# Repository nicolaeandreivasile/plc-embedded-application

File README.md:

# plc-embedded-application
A PLC (Programmable Logic Controller) made from scratch focused on controlling and maintaining industrial-like applications

## Board design
Control unit schematic under development. I/O unit schematic development process not started yet

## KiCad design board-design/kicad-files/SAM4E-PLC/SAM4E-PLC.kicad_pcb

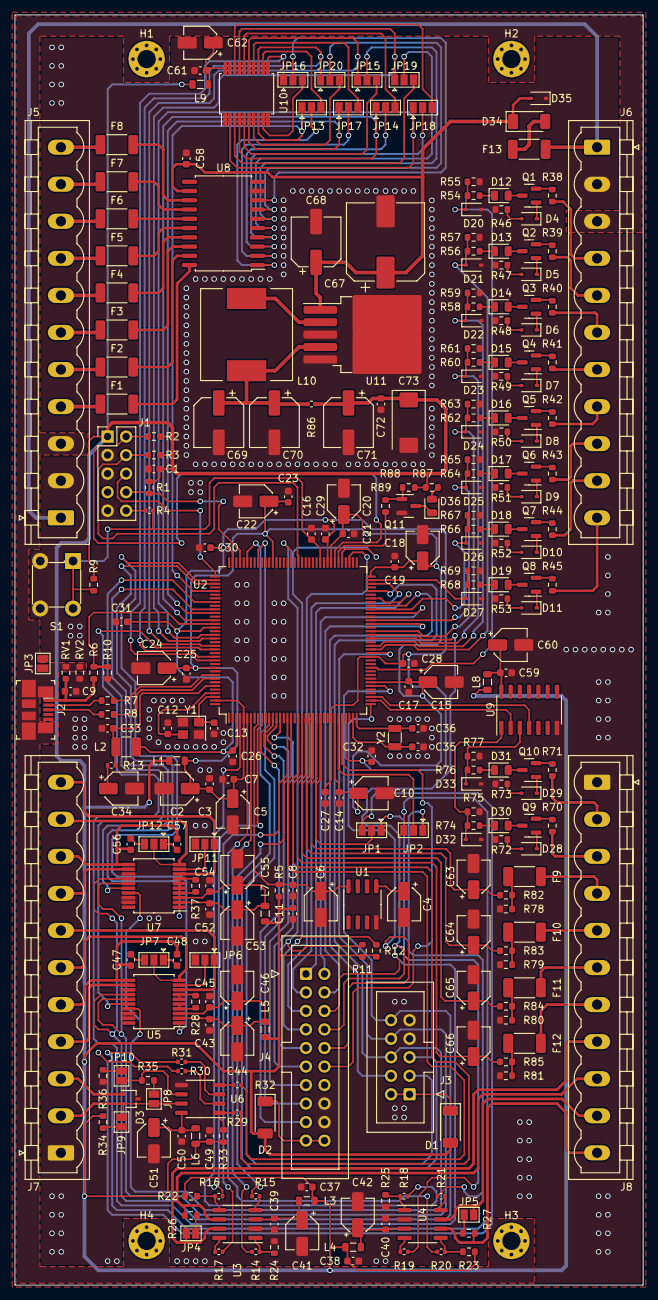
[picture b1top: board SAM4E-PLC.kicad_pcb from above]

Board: 2 copper layers, 86.1 x 174.1 mm, 280 parts (0 on the bottom side), 247 nets.

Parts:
C1, C37, C38, C49, C72: 22uF/6.3V/20%/C0603; C_0603_1608Metric
C2, C5, C10, C15, C18, C20, C22, C24, C34, C41, C42, C44, C46, C51, C53, C55, C60, C62: 10uF/16V/20%/4x5.4mm; CP_Elec_4x5.4
C3, C7, C14, C17, C19, C21, C23, C25, C26, C27, C28, C29, C30, C31, C32, C33, C39, C40, C43, C45, C47, C48, C50, C52, C54, C56, C57, C59, C61: 0.1uF/6.3V/20%/C0603; C_0603_1608Metric
C4, C6, C63, C64, C65, C66: 1uF/16V/20%/4x5.4mm; CP_Elec_4x5.4
C8, C11, C16: 100nF/6.3V/20%/C0603; C_0603_1608Metric
C9: 10pF/6.3V/20%/C0603; C_0603_1608Metric
C12, C13, C35, C36: 12pF/6.3V/10%/C0603; C_0603_1608Metric
C58: 47uF/6.3V/20%/C0603; C_0603_1608Metric
C67: 100uF/63V/20%/10x12.5mm (APD1012101M063R); CP_Elec_10x12.5
C68: 22uF/63V/20%/6.3x6mm (APD0606220M063R); CP_Elec_6.3x5.9
C69: 220uF/16V/20%/6.3x7.7mm; CP_Elec_6.3x7.7
C70, C71: 100uF/16V/20%/6.3x7.7mm; CP_Elec_6.3x7.7
C73: 470uF/16V/20%/C2917/Tantalum; CP_EIA-7343-30_AVX-N
D1, D2: RB068LAM-30TFTR; D_SOD-128
D3: VESD16A2-03G-G3; SOT-323_SC-70
D4, D5, D6, D7, D8, D9, D10, D11, D28, D29: CMDZ12V; D_SOD-323
D12, D13, D14, D15, D16, D17, D18, D19, D30, D31, D36: LED; LED_0805_2012Metric
D20, D21, D22, D23, D24, D25, D26, D27, D32, D33: CMDZ3V6; D_SOD-323
D34: RB088LAM-40TFTR; D_SOD-128
D35: SD36C-01FTG; D_SOD-323
F1, F2, F3, F4, F5, F6, F7, F8, F9, F10, F11, F12, F13: MF-SMDF050; Fuse_2010_5025Metric
H1, H2, H3, H4: MountingHole; MountingHole_2.5mm_Pad_Via
J1: Conn_ARM_JTAG_SWD_10; PinHeader_2x05_P2.54mm_Vertical
J2: 0473460001; USB_Micro_B_Female_0473460001
J3: Conn_02x05_Odd_Even; IDC-Header_2x05_P2.54mm_Vertical
J4: Conn_02x10_Odd_Even; IDC-Header_2x10_P2.54mm_Vertical
J5, J6, J7, J8: Screw_Terminal_01x11; PhoenixContact_MSTBVA_2,5_11-G-5,08_1x11_P5.08mm_Vertical
JP1, JP2, JP6, JP7, JP11, JP12, JP13, JP14, JP15, JP16, JP17, JP18, JP19, JP20: SolderJumper_3_Open; SolderJumper-3_P1.3mm_Open_Pad1.0x1.5mm
JP3, JP4, JP5, JP8, JP9, JP10: SolderJumper_2_Open; SolderJumper-2_P1.3mm_Open_Pad1.0x1.5mm
L1, L3, L4, L5, L6, L7, L8, L9: FB0805/600R/2A; L_0805_2012Metric
L2: 10uH; L_1210_3225Metric
L10: 150uH/12x12mm (SRR1210-151M); L_12x12mm_H8mm
Q1, Q2, Q3, Q4, Q5, Q6, Q7, Q8, Q9, Q10: BC807; SOT-23
Q11: BC817; SOT-23
R1, R2, R3: 100K/R0603; R_0603_1608Metric
R4, R14, R15, R16, R17, R18, R19, R20, R21, R29, R30, R31, R32, R86: 0R(board_mounted); R_0402_1005Metric
R5, R87: 330R/R0603; R_0603_1608Metric
R6: 47K/R0603; R_0603_1608Metric
R7, R8: 27R/R0603; R_0603_1608Metric
R9, R11, R12, R22, R23, R24, R25, R33, R46, R47, R48, R49, R50, R51, R52, R53, R55, R57, R59, R61, R63, R65, R67, R69, R72, R73, R75, R77, R82, R83, R84, R85, R88: 10K/R0603; R_0603_1608Metric
R10: 68K/R0603; R_0603_1608Metric
R13: 1R/R0402; R_0402_1005Metric
R26, R27, R35: 120R/R0603; R_0603_1608Metric
R28, R37: 400R/R0603; R_0603_1608Metric
R34, R36: 420R/R0603; R_0603_1608Metric
R38, R39, R40, R41, R42, R43, R44, R45, R70, R71: 100R/R0603; R_0603_1608Metric
R54, R56, R58, R60, R62, R64, R66, R68, R74, R76: 4.3K/R0603; R_0603_1608Metric
R78, R79, R80, R81: 100R/1W/R0603; R_0603_1608Metric
R89: 1K/R0603; R_0603_1608Metric
RV1, RV2: V5.5MLA0603N; R_0603_1608Metric
S1: 1825910-6; Switch_Tactile_THT_6x6mm
U1: LM385M-ADJ; SOIC-8_3.9x4.9mm_P1.27mm
U2: ATSAM4E16E; LQFP-144_20x20mm_P0.5mm
U3, U4: SN65HVD234; SOIC-8_3.9x4.9mm_P1.27mm
U5, U7: MAX31865xAP; SSOP-20_5.3x7.2mm_P0.65mm
U6: MAX3485ESA+T; SO-8_3.9x4.9mm_P1.27mm
U8: ULN2803CDWR; SOIC-20W_7.5x12.8mm_P1.27mm
U9: 74AC14SCX; SOIC-14_3.9x8.7mm_P1.27mm
U10: SN74HC240DBR; SSOP-20_5.3x7.2mm_P0.65mm
U11: LM2576HVS-3.3; TO-263-5_TabPin3
Y1: ECS-160-8-33B-CTN-TR; Crystal_SMD_3225-4Pin_3.2x2.5mm
Y2: FC-135 32.7680KA-AG0; Crystal_SMD_3215-2Pin_3.2x1.5mm

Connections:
+3V3: C1.1, C11.1, C37.1, C38.1, C49.1, C71.1, C72.1, C73.1, D1.2 (A), D2.2 (A), J1.1 (VTref), L1.1, L3.1, L4.1, L5.1, L6.1, L7.1, L8.1, L9.1, R1.2, R2.2, R3.2, R5.1, R9.1, R11.1, R12.1, R22.1, R23.1, R33.1, R34.1, R86.2, R87.1, R88.1
+24V: C58.1, C67.1, C68.1, D34.1 (K), D35.2 (A2), U8.12 (COM), U11.1 (VIN)
/CAN0_D: JP1.1 (A), R19.1
/CAN0_EN: R20.1, U2.6 (PE1)
/CAN0_R: JP2.1 (A), R21.1
/CAN0_RS: R18.1, U2.4 (PE0)
/CAN1_D: R15.1, U2.18 (PC15)
/CAN1_EN: R16.1, U2.10 (PE3)
/CAN1_R: R17.1, U2.17 (PC12)
/CAN1_RS: R14.1, U2.7 (PE2)
/CNT0: U2.38 (PC1), U9.2 (~O0)
/CNT1: U2.39 (PC2), U9.4 (~O1)
/ESP32_INT: J3.5, U2.103 (PC17)
/I2C_SCL: J4.7, R12.2, U2.77 (PA4/PGMNCMD)
/I2C_SDA: J4.9, R11.2, U2.91 (PA3)
/IO/AI0: C66.1, R85.2, U2.22 (PA20/PGMD8)
/IO/AI1: C65.1, R84.2, U2.23 (PA19/PGMD7)
/IO/AI2: C64.1, R83.2, U2.24 (PA18/PGMD6)
/IO/AI3: C63.1, R82.2, U2.25 (PA17/PGMD5)
/IO/DI0: D20.1 (K), R54.2, R55.1, U2.47 (PD27)
/IO/DI1: D21.1 (K), R56.2, R57.1, U2.52 (PD25)
/IO/DI2: D22.1 (K), R58.2, R59.1, U2.53 (PD26)
/IO/DI3: D23.1 (K), R60.2, R61.1, U2.55 (PD24)
/IO/DI4: D24.1 (K), R62.2, R63.1, U2.57 (PD23)
/IO/DI5: D25.1 (K), R64.2, R65.1, U2.60 (PD22)
/IO/DI6: D26.1 (K), R66.2, R67.1, U2.63 (PD21)
/IO/DI7: D27.1 (K), R68.2, R69.1, U2.71 (PD28)
/IO/DO0: JP18.1 (A), U2.125 (PD5), U10.2 (1A1)
/IO/DO1: JP14.1 (A), U2.121 (PD6), U10.4 (1A2)
/IO/DO2: JP17.1 (A), U2.119 (PD7), U10.6 (1A3)
/IO/DO3: JP13.1 (A), U2.113 (PD8), U10.8 (1A4)
/IO/DO4: JP16.1 (A), U2.132 (PD1), U10.11 (2A1)
/IO/DO5: JP20.1 (A), U2.131 (PD2), U10.13 (2A2)
/IO/DO6: JP15.1 (A), U2.128 (PD3), U10.15 (2A3)
/IO/DO7: JP19.1 (A), U2.126 (PD4), U10.17 (2A4)
/IO/MCV_AI0: F12.1, J8.7
/IO/MCV_AI1: F11.1, J8.6
/IO/MCV_AI2: F10.1, J8.5
/IO/MCV_AI3: F9.1, J8.4
/IO/MCV_CNT0: J8.2, R71.1
/IO/MCV_CNT1: J8.3, R70.1
/IO/MCV_DI0: J6.4, R38.1
/IO/MCV_DI1: J6.5, R39.1
/IO/MCV_DI2: J6.6, R40.1
/IO/MCV_DI3: J6.7, R41.1
/IO/MCV_DI4: J6.8, R42.1
/IO/MCV_DI5: J6.9, R43.1
/IO/MCV_DI6: J6.10, R44.1
/IO/MCV_DI7: J6.11, R45.1
/IO/MCV_DO0: F4.2, J5.7
/IO/MCV_DO1: F3.2, J5.6
/IO/MCV_DO2: F2.2, J5.5
/IO/MCV_DO3: F1.2, J5.4
/IO/MCV_DO4: F8.2, J5.11
/IO/MCV_DO5: F7.2, J5.10
/IO/MCV_DO6: F6.2, J5.9
/IO/MCV_DO7: F5.2, J5.8
/IO/~DO0: JP18.3 (B), U10.18 (1Y1)
/IO/~DO1: JP14.3 (B), U10.16 (1Y2)
/IO/~DO2: JP17.3 (B), U10.14 (1Y3)
/IO/~DO3: JP13.3 (B), U10.12 (1Y4)
/IO/~DO4: JP16.3 (B), U10.9 (2Y1)
/IO/~DO5: JP20.3 (B), U10.7 (2Y2)
/IO/~DO6: JP15.3 (B), U10.5 (2Y3)
/IO/~DO7: JP19.3 (B), U10.3 (2Y4)
/LTE_AP_READY: J4.11, U2.15 (PC30)
/LTE_PWRKEY: J4.15, U2.13 (PC26)
/LTE_RESET_N: J4.17, U2.12 (PC27)
/LTE_STATUS: J4.13, U2.14 (PC31)
/LTE_UART_CTS: J4.4, U2.59 (PA25/PGMD13)
/LTE_UART_DBG_RXD: J4.5, U2.75 (PA9/PGMM1)
/LTE_UART_DBG_TXD: J4.1, U2.66 (PA10/PGMM2)
/LTE_UART_DCD: J4.2, U2.62 (PA26/PGMD14)
/LTE_UART_DTR: J4.3, U2.70 (PA27/PGMD15)
/LTE_UART_RI: J4.6, U2.129 (PA29)
/LTE_UART_RTS: J4.8, U2.56 (PA24/PGMD12)
/LTE_UART_RXD: J4.12, U2.32 (PA21/PGMD9)
/LTE_UART_TXD: J4.10, U2.37 (PA22/PGMD10)
/PWR_LED: R89.2, U2.78 (PD16)
/RS_DE: JP2.3 (B), R31.1
/RS_DI: R32.1, U2.20 (PB1)
/RS_RO: R29.1, U2.21 (PB0)
/SAM4E_INT: J3.3, U2.100 (PC16)
/SPI_CS0: J3.4, U2.64 (PA11/PGMM3)
/SPI_CS1: U2.118 (PA31), U7.16 (~CS)
/SPI_CS2: U2.116 (PA30), U5.16 (~CS)
/SPI_MISO: J3.6, U2.68 (PA12/PGMD0), U5.17 (SDO), U7.17 (SDO)
/SPI_MOSI: J3.10, U2.42 (PA13/PGMD1), U5.14 (SDI), U7.14 (SDI)
/SPI_SCK: J3.8, U2.51 (PA14/PGMD2), U5.15 (SCLK), U7.15 (SCLK)
/VBUS: R6.2, R10.1, U2.122 (PC21)
/~NRST: C16.1, R4.2, R9.2, S1.1, S1.2, U2.83 (~NRST)
/~RS_RE: JP1.3 (B), R30.1
/~RTD0_DRDY: U2.110 (PD9), U5.1 (~DRDY)
/~RTD1_DRDY: U2.111 (PC18), U7.1 (~DRDY)
Earth_Protective: J2.SH, J5.3, J6.3, JP3.2 (B), RV1.2, RV2.2
GND: C1.2, C2.2, C3.2, C4.2, C5.2, C6.2, C7.2, C8.2, C9.2, C10.2, C11.2, C12.1, C13.1, C14.2, C15.2, C16.2, C17.2, C18.2, C19.2, C20.2, C21.2, C22.2, C23.2, C24.2, C25.2, C26.2, C27.2, C28.2, C29.2, C30.2, C31.2, C32.2, C33.2, C34.2, C35.1, C36.1, C37.2, C38.2, C39.2, C40.2, C41.2, C42.2, C43.2, C44.2, C45.2, C46.2, C49.2, C50.2, C51.2, C52.2, C53.2, C54.2, C55.2, C58.2, C59.2, C60.2, C61.2, C62.2, C63.2, C64.2, C65.2, C66.2, C67.2, C68.2, C69.2, C70.2, C71.2, C72.2, C73.2, D3.3 (common), D20.2 (A), D21.2 (A), D22.2 (A), D23.2 (A), D24.2 (A), D25.2 (A), D26.2 (A), D27.2 (A), D32.2 (A), D33.2 (A), D35.1 (A1), J1.3 (GND), J1.5 (GND), J1.9 (GNDDetect), J2.5, J3.7, J3.9, J4.16, J4.18, J5.2, J6.2, J7.1, J8.1, JP3.1 (A), JP6.3 (B), JP11.3 (B), Q11.2 (E), R10.2, R24.2, R25.2, R36.1, R46.2, R47.2, R48.2, R49.2, R50.2, R51.2, R52.2, R53.2, R55.2, R57.2, R59.2, R61.2, R63.2, R65.2, R67.2, R69.2, R72.2, R73.2, R75.2, R77.2, R78.1, R79.1, R80.1, R81.1, RV2.1, S1.3, S1.4, U1.4 (A), U2.8 (GND), U2.44 (GND), U2.61 (GND), U2.95 (GND), U2.115 (GND), U2.135 (GND), U2.138 (GND), U3.2 (GND), U4.2 (GND), U5.13 (GND), U5.18 (DGND), U5.19 (GND), U6.5 (GND), U7.13 (GND), U7.18 (DGND), U7.19 (GND), U8.9 (GND), U9.7 (GND), U10.1 (~1OE), U10.10 (GND), U10.19 (~2OE), U11.3 (GND), U11.5 (~ON/OFF), Y1.2, Y1.4
MCV_CAN0_H: J8.10, JP5.2 (B), U4.7 (CANH)
MCV_CAN0_L: J8.11, R27.1, U4.6 (CANL)
MCV_CAN1_H: J8.8, JP4.2 (B), U3.7 (CANH)
MCV_CAN1_L: J8.9, R26.1, U3.6 (CANL)
MCV_RS_A: D3.1 (A1), J7.3, JP10.2 (B), R35.1, U6.6 (A)
MCV_RS_B: D3.2 (A2), J7.2, JP8.2 (B), JP9.1 (A), U6.7 (B)
MCV_RTD0_FORCE+: J7.7, JP6.1 (A), U5.8 (FORCE+)
MCV_RTD0_FORCE-: J7.4, U5.12 (FORCE-)
MCV_RTD0_RTDIN+: J7.6, JP7.2 (C), U5.10 (RTDIN+)
MCV_RTD0_RTDIN-: C47.1, C48.1, J7.5, U5.11 (RTDIN-)
MCV_RTD1_FORCE+: J7.11, JP11.1 (A), U7.8 (FORCE+)
MCV_RTD1_FORCE-: J7.8, U7.12 (FORCE-)
MCV_RTD1_RTDIN+: J7.10, JP12.2 (C), U7.10 (RTDIN+)
MCV_RTD1_RTDIN-: C56.1, C57.1, J7.9, U7.11 (RTDIN-)
unnamed: C9.1, J2.1, R6.1, RV1.1
unnamed: C34.1, R13.2
unnamed: D1.1 (K), J3.1, J3.2
unnamed: D2.1 (K), J4.19, J4.20
unnamed: D4.2 (A), R46.1
unnamed: D4.1 (K), Q1.1 (B)
unnamed: D5.2 (A), R47.1
unnamed: D5.1 (K), Q2.1 (B)
unnamed: D6.2 (A), R48.1
unnamed: D6.1 (K), Q3.1 (B)
unnamed: D7.2 (A), R49.1
unnamed: D7.1 (K), Q4.1 (B)
unnamed: D8.2 (A), R50.1
unnamed: D8.1 (K), Q5.1 (B)
unnamed: D9.2 (A), R51.1
unnamed: D9.1 (K), Q6.1 (B)
unnamed: D10.2 (A), R52.1
unnamed: D10.1 (K), Q7.1 (B)
unnamed: D11.2 (A), R53.1
unnamed: D11.1 (K), Q8.1 (B)
unnamed: D12.2 (A), Q1.3 (C)
unnamed: D12.1 (K), R54.1
unnamed: D13.2 (A), Q2.3 (C)
unnamed: D13.1 (K), R56.1
unnamed: D14.2 (A), Q3.3 (C)
unnamed: D14.1 (K), R58.1
unnamed: D15.2 (A), Q4.3 (C)
unnamed: D15.1 (K), R60.1
unnamed: D16.2 (A), Q5.3 (C)
unnamed: D16.1 (K), R62.1
unnamed: D17.2 (A), Q6.3 (C)
unnamed: D17.1 (K), R64.1
unnamed: D18.2 (A), Q7.3 (C)
unnamed: D18.1 (K), R66.1
unnamed: D19.2 (A), Q8.3 (C)
unnamed: D19.1 (K), R68.1
unnamed: D28.2 (A), R72.1
unnamed: D28.1 (K), Q9.1 (B)
unnamed: D29.2 (A), R73.1
unnamed: D29.1 (K), Q10.1 (B)
unnamed: D30.2 (A), Q9.3 (C)
unnamed: D30.1 (K), R74.1
unnamed: D31.2 (A), Q10.3 (C)
unnamed: D31.1 (K), R76.1
unnamed: D32.1 (K), R74.2, R75.1, U9.1 (I0)
unnamed: D33.1 (K), R76.2, R77.1, U9.3 (I1)
unnamed: D34.2 (A), F13.2
unnamed: D36.2 (A), R87.2
unnamed: D36.1 (K), Q11.3 (C)
unnamed: F9.2, R78.2, R82.1
unnamed: F10.2, R79.2, R83.1
unnamed: F11.2, R80.2, R84.1
unnamed: F12.2, R81.2, R85.1
unnamed: J1.8 (NC/TDI), R1.1, U2.105 (PB4)
unnamed: J1.4 (SWCLK/TCK), R3.1, U2.89 (PB7)
unnamed: J1.2 (SWDIO/TMS), R2.1, U2.79 (PB6)
unnamed: J1.6 (SWO/TDO), U2.109 (PB5)
unnamed: J1.10 (~RESET), R4.1
unnamed: J2.2, R7.1
unnamed: J2.3, R8.1
unnamed: JP1.2 (C), U2.26 (PB2)
unnamed: JP2.2 (C), U2.31 (PB3)
unnamed: JP4.1 (A), R26.2
unnamed: JP5.1 (A), R27.2
unnamed: JP6.2 (C), U5.9 (FORCE2)
unnamed: C48.2, JP7.1 (A)
unnamed: C47.2, JP7.3 (B)
unnamed: JP8.1 (A), R35.2
unnamed: JP9.2 (B), R34.2
unnamed: JP10.1 (A), R36.2
unnamed: JP11.2 (C), U7.9 (FORCE2)
unnamed: C57.2, JP12.1 (A)
unnamed: C56.2, JP12.3 (B)
unnamed: JP13.2 (C), U8.1 (1B)
unnamed: JP14.2 (C), U8.3 (3B)
unnamed: JP15.2 (C), U8.6 (6B)
unnamed: JP16.2 (C), U8.8 (8B)
unnamed: JP17.2 (C), U8.2 (2B)
unnamed: JP18.2 (C), U8.4 (4B)
unnamed: JP19.2 (C), U8.5 (5B)
unnamed: JP20.2 (C), U8.7 (7B)
unnamed: Q1.2 (E), R38.2
unnamed: Q2.2 (E), R39.2
unnamed: Q3.2 (E), R40.2
unnamed: Q4.2 (E), R41.2
unnamed: Q5.2 (E), R42.2
unnamed: Q6.2 (E), R43.2
unnamed: Q7.2 (E), R44.2
unnamed: Q8.2 (E), R45.2
unnamed: Q9.2 (E), R70.2
unnamed: Q10.2 (E), R71.2
unnamed: Q11.1 (B), R88.2, R89.1
unnamed: C4.1, U1.5 (FB)
unnamed: C6.1, C8.1, R5.2, U1.8 (K), U2.9 (ADVREFP)
unnamed: C35.2, U2.35 (PA7/PGMNVALID), Y2.2
unnamed: C36.2, U2.36 (PA8/PGMM0), Y2.1
unnamed: C12.2, U2.141 (PB8), Y1.3
unnamed: C13.2, U2.142 (PB9), Y1.1
unnamed: R7.2, U2.136 (PB10)
unnamed: R8.2, U2.137 (PB11)
unnamed: C2.1, C3.1, C5.1, C7.1, C10.1, C14.1, C15.1, C17.1, C18.1, C19.1, C20.1, C21.1, C22.1, C23.1, C24.1, C25.1, L1.2, U2.5 (VDDIN), U2.30 (VDDIO), U2.43 (VDDIO), U2.72 (VDDIO), U2.80 (VDDIO), U2.96 (VDDIO), U2.134 (VDDIO), U2.143 (VDDIO)
unnamed: C26.1, C27.1, C28.1, C29.1, C30.1, C31.1, C32.1, L2.1, U2.3 (VDDOUT), U2.29 (VDDCORE), U2.33 (VDDCORE), U2.50 (VDDCORE), U2.81 (VDDCORE), U2.107 (VDDCORE), U2.123 (VDDCORE)
unnamed: C33.1, L2.2, R13.1, U2.139 (VDDPLL)
unnamed: R14.2, R24.1, U3.1 (D)
unnamed: R16.2, R22.2, U3.5 (EN)
unnamed: R15.2, U3.4 (R)
unnamed: R17.2, U3.8 (Rs)
unnamed: C39.1, C41.1, L3.2, U3.3 (VCC)
unnamed: R18.2, R25.1, U4.1 (D)
unnamed: R20.2, R23.2, U4.5 (EN)
unnamed: R19.2, U4.4 (R)
unnamed: R21.2, U4.8 (Rs)
unnamed: C40.1, C42.1, L4.2, U4.3 (VCC)
unnamed: R28.1, U5.4 (BIAS), U5.5 (REFIN+)
unnamed: C43.1, C44.1, C45.1, C46.1, L5.2, U5.2 (DVDD), U5.3 (VDD)
unnamed: R28.2, U5.6 (REFIN-), U5.7 (ISENSOR)
unnamed: R31.2, U6.3 (DE)
unnamed: R32.2, U6.4 (DI)
unnamed: R29.2, R33.2, U6.1 (RO)
unnamed: C50.1, C51.1, L6.2, U6.8 (VCC)
unnamed: R30.2, U6.2 (~RE)
unnamed: R37.1, U7.4 (BIAS), U7.5 (REFIN+)
unnamed: C52.1, C53.1, C54.1, C55.1, L7.2, U7.2 (DVDD), U7.3 (VDD)
unnamed: R37.2, U7.6 (REFIN-), U7.7 (ISENSOR)
unnamed: F1.1, U8.20 (1C)
unnamed: F2.1, U8.19 (2C)
unnamed: F3.1, U8.18 (3C)
unnamed: F4.1, U8.17 (4C)
unnamed: F5.1, U8.16 (5C)
unnamed: F6.1, U8.15 (6C)
unnamed: F7.1, U8.14 (7C)
unnamed: F8.1, U8.13 (8C)
unnamed: C59.1, C60.1, L8.2, U9.14 (VCC)
unnamed: C61.1, C62.1, L9.2, U10.20 (VCC)
unnamed: C69.1, C70.1, L10.2, R86.1, U11.4 (FB)
unnamed: L10.1, U11.2 (OUT)
VIN_24V: F13.1, J5.1, J6.1

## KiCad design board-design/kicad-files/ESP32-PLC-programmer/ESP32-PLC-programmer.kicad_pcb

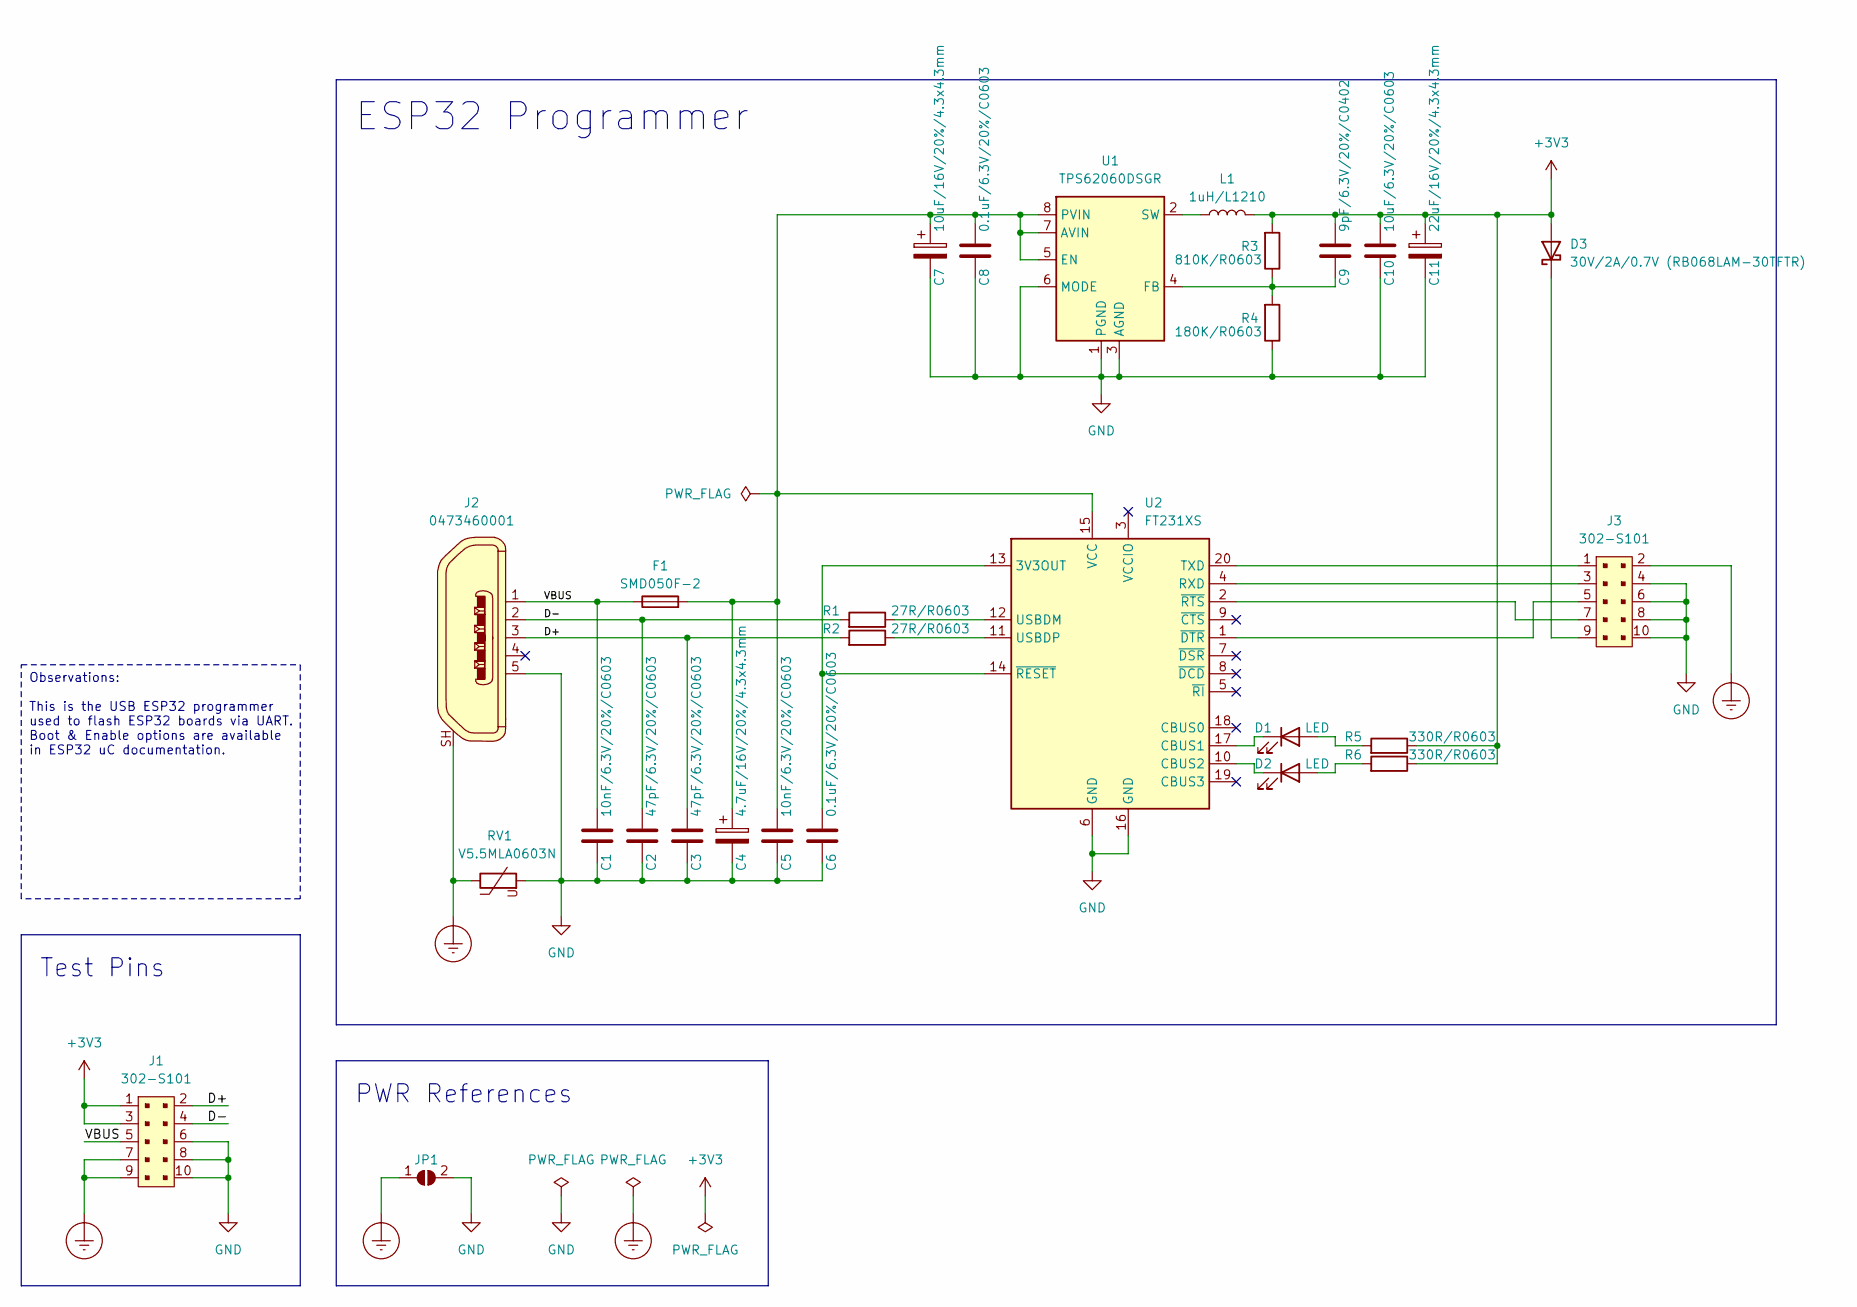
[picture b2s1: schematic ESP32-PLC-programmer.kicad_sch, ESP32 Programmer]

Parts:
C1, C5: 10nF/6.3V/20%/C0603; C_0603_1608Metric
C2, C3: 47pF/6.3V/20%/C0603; C_0603_1608Metric
C4: 4.7uF/16V/20%/4.3x4.3mm; CP_Elec_4x5.4
C6, C8: 0.1uF/6.3V/20%/C0603; C_0603_1608Metric
C7: 10uF/16V/20%/4.3x4.3mm; CP_Elec_4x5.4
C9: 9pF/6.3V/20%/C0402; C_0402_1005Metric
C10: 10uF/6.3V/20%/C0603; C_0603_1608Metric
C11: 22uF/16V/20%/4.3x4.3mm; CP_Elec_4x5.4
D1, D2: LED; LED_0805_2012Metric
D3: 30V/2A/0.7V (RB068LAM-30TFTR); D_SOD-128
F1: SMD050F-2; Fuse_2920_7451Metric
J1, J3: 302-S101; IDC-Header_2x05_P2.54mm_Vertical; MPN 302-S101; Digi-Key_PN ED1543-ND
J2: 0473460001; USB_Micro_B_Female_0473460001; MPN 0473460001; Digi-Key_PN WM17141CT-ND
JP1: SolderJumper_2_Open; SolderJumper-2_P1.3mm_Open_Pad1.0x1.5mm
L1: 1uH/L1210; L_1210_3225Metric
R1, R2: 27R/R0603; R_0603_1608Metric
R3: 810K/R0603; R_0603_1608Metric
R4: 180K/R0603; R_0603_1608Metric
R5, R6: 330R/R0603; R_0603_1608Metric
RV1: V5.5MLA0603N; R_0603_1608Metric
U1: TPS62060DSGR; WSON-8-1EP_2x2mm_P0.5mm_EP0.9x1.6mm_ThermalVias
U2: FT231XS; SSOP-20_3.9x8.7mm_P0.635mm

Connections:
+3V3: C9.1, C10.1, C11.1, D3.2 (A), J1.1, J1.3, L1.2, R3.2, R5.1, R6.1
/D+: C3.1, J1.2, J2.3, R2.2
/D-: C2.1, J1.4, J2.2, R1.2
/VBUS: C1.1, F1.1, J1.5, J2.1
Earth_Protective: J1.7, J1.9, J2.SH, J3.2, JP1.1 (A), RV1.1
GND: C1.2, C2.2, C3.2, C4.2, C5.2, C6.2, C7.2, C8.2, C10.2, C11.2, J1.6, J1.8, J1.10, J2.5, J3.4, J3.6, J3.8, J3.10, JP1.2 (B), R4.1, RV1.2, U1.1 (PGND), U1.3 (AGND), U1.6 (MODE), U2.6 (GND), U2.16 (GND)
unnamed: D1.2 (A), R5.2
unnamed: D1.1 (K), U2.17 (CBUS1)
unnamed: D2.2 (A), R6.2
unnamed: D2.1 (K), U2.10 (CBUS2)
unnamed: D3.1 (K), J3.9
unnamed: C4.1, C5.1, C7.1, C8.1, F1.2, U1.5 (EN), U1.7 (AVIN), U1.8 (PVIN), U2.15 (VCC)
unnamed: C9.2, R3.1, R4.2, U1.4 (FB)
unnamed: L1.1, U1.2 (SW)
unnamed: C6.1, U2.13 (3V3OUT), U2.14 (~RESET)
unnamed: J3.3, U2.4 (RXD)
unnamed: J3.1, U2.20 (TXD)
unnamed: R1.1, U2.12 (USBDM)
unnamed: R2.1, U2.11 (USBDP)
unnamed: J3.5, U2.1 (~DTR)
unnamed: J3.7, U2.2 (~RTS)

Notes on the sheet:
Observations: This is the USB ESP32 programmer used to flash ESP32 boards via UART. Boot & Enable options are available in ESP32 uC documentation.
PWR References
Test Pins
ESP32 Programmer

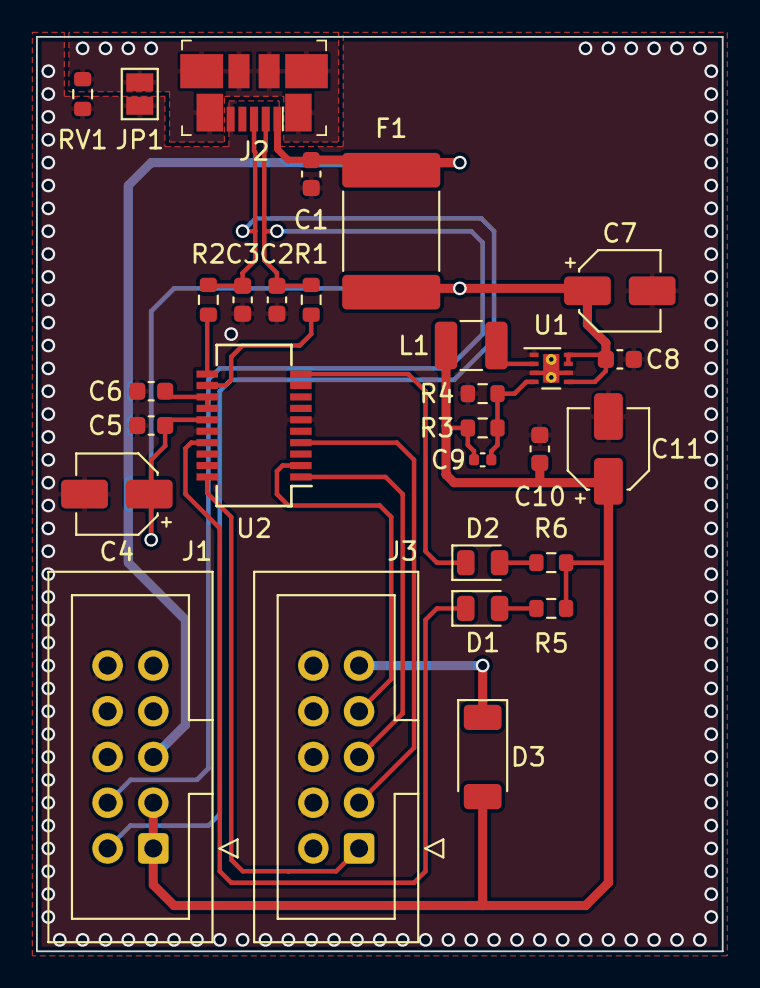
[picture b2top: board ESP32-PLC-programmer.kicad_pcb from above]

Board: 2 copper layers, 38.1 x 50.8 mm, 29 parts (0 on the bottom side), 21 nets.

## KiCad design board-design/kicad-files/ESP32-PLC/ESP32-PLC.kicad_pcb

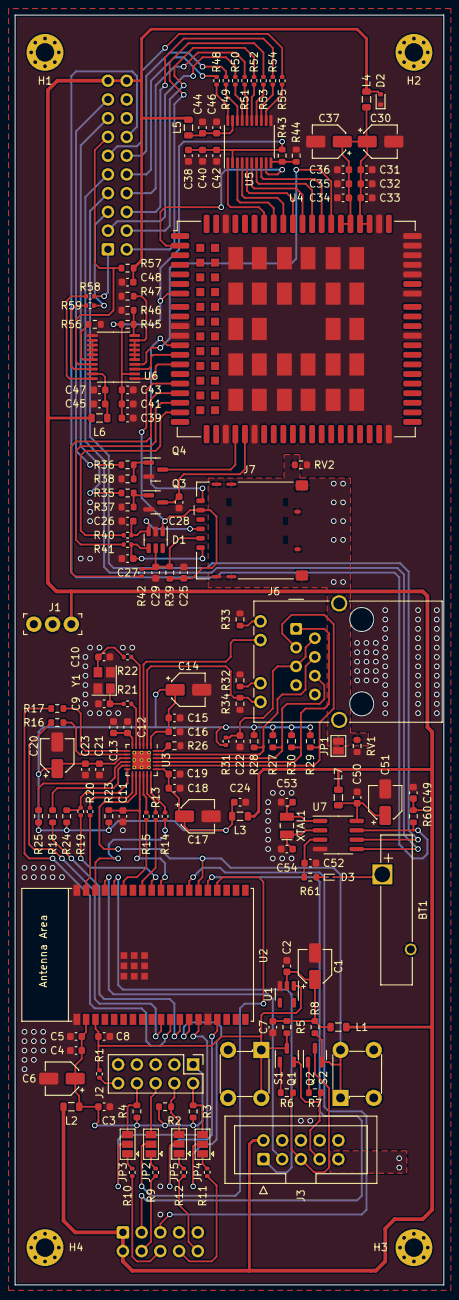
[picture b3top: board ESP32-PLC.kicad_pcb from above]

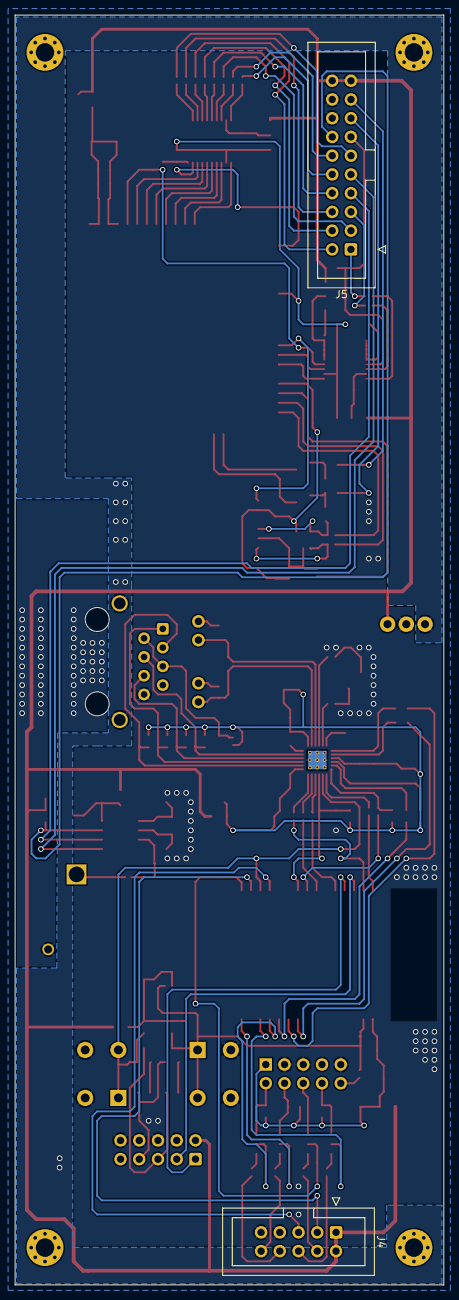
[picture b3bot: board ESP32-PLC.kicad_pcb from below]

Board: 2 copper layers, 58.1 x 172.1 mm, 159 parts (2 on the bottom side), 129 nets.

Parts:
BT1: CR2032 (Panasonic vertical); Battery_Panasonic_CR2032-VS1N_Vertical_CircularHoles
C1, C6, C14, C17, C20: 22uF/16V/20%/4.3x4.3mm; CP_Elec_4x5.4
C2, C4, C16, C19, C23, C25, C31, C36, C42, C43, C44, C45, C50, C52: 0.1uF/6.3V/20%/C0603; C_0603_1608Metric
C3, C7, C24, C48, C49: 22uF/6.3V/20%/C0603; C_0603_1608Metric
C5, C8, C12, C15, C18, C21, C38, C39: 1uF/6.3V/20%/C0603; C_0603_1608Metric
C9, C10: 25pF/6.3V/10%/C0603; C_0603_1608Metric
C11: 1nF/6.3V/20%/C0603; C_0603_1608Metric
C13, C22: 470pF/6.3V/20%/C0603; C_0603_1608Metric
C26, C27, C29, C32, C35: 33pF/6.3V/20%/C0603; C_0603_1608Metric
C28: 10nF/6.3V/20%/C0603; C_0603_1608Metric
C30, C37: 100uF/16V/20%/4x5.4mm; CP_Elec_4x5.4
C33, C34: 10pF/6.3V/20%/C0603; C_0603_1608Metric
C40, C41, C46, C47: 10uF/6.3V/20%/C0603; C_0603_1608Metric
C51: 10uF/16V/20%/4x5.4mm; CP_Elec_4x5.4
C53, C54: 10pF/6.3V/10%/C0603; C_0603_1608Metric
D1: ESDA6V1-5SC6; SOT-23-6
D2: VESD05C1-02V; D_SOD-523
D3: 20V/0.5A/0.5V (NSR0620P2T5G); D_SOD-923
H1, H2, H3, H4: MountingHole; MountingHole_2.5mm_Pad_Via
J1: 640456-3; PinHeader_1x3_P2.54_Drill1.1mm
J2: Conn_ARM_JTAG_SWD_10; PinHeader_2x05_P2.54mm_Vertical
J3: 302-S101; IDC-Header_2x05_P2.54mm_Vertical
J4: Conn_02x05_Odd_Even; IDC-Header_2x05_P2.54mm_Vertical
J5: Conn_02x10_Odd_Even; IDC-Header_2x10_P2.54mm_Vertical
J6: RJ45_Wuerth_7499010121A; RJ45_Wuerth_7499010121A_Horizontal
J7: SF53S006VCBR2000; microSIM_JAE_SF53S006VCBR2000
JP1: SolderJumper_2_Open; SolderJumper-2_P1.3mm_Open_Pad1.0x1.5mm
JP2, JP3, JP4, JP5: SolderJumper_3_Open; SolderJumper-3_P1.3mm_Open_Pad1.0x1.5mm
L1, L2, L3, L4, L5, L6, L7: FB0805/600R/2A; L_0805_2012Metric
Q1, Q2, Q3, Q4: BC817; SOT-23
R1, R9, R10, R11, R12, R13, R14, R15, R19, R20, R21, R22, R31, R40, R41, R42, R48, R49, R50, R51, R52, R53, R54, R55, R58, R59: 0R(board_mounted); R_0402_1005Metric
R2, R3, R4: 100K/R0603; R_0603_1608Metric
R5, R6, R7, R8, R23, R25, R34, R43, R45, R57, R60, R61: 10K/R0603; R_0603_1608Metric
R16, R17, R18: 10R/R0603; R_0603_1608Metric
R24: 1K/R0603; R_0603_1608Metric
R26: 12.1K/1%/R0603; R_0603_1608Metric
R27, R28, R29, R30: 49.9R/1%/R0603; R_0603_1608Metric
R32, R33: 330R/R0603; R_0603_1608Metric
R35, R36: 4.7K/R0603; R_0603_1608Metric
R37, R38: 47K/R0603; R_0603_1608Metric
R39: 15K/R0603; R_0603_1608Metric
R44, R46: 120K/R0603; R_0603_1608Metric
R47, R56: 51K/R0603; R_0603_1608Metric
RV1, RV2: V5.5MLA0603N; R_0603_1608Metric
S1, S2: 1825910-6; Switch_Tactile_THT_6x6mm
U1: BD48ExxG; SOT-23-5
U2: ESP32-WROVER-E
U3: LAN8720A; VQFN-24-1EP_4x4mm_P0.5mm_EP2.5x2.5mm_ThermalVias
U4: EC21; Quectel_EC21_L29.0mm_W32.0mm
U5, U6: TXS0108EPW; TSSOP-20_4.4x6.5mm_P0.65mm
U7: MCP7940N-xSN; SOIC-8_3.9x4.9mm_P1.27mm
XTAL1: ECS-_327-7-34B-TR; SMD-2_3.2x1.5mm
Y1: Q25MHz/20ppm/3.2x2.5mm (FL2500213Z); Crystal_SMD_3225-4Pin_3.2x2.5mm

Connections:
+3V3: C48.1, C49.1, D2.2 (A2), J1.3, J3.2, J4.1, J4.2, J5.19, J5.20, L1.1, L2.1, L3.2, L4.1, L5.2, L6.2, L7.1, R57.2, R60.1
/CS0: JP2.1 (A), R9.1
/ESP32_INT: J4.5, U2.26 (ADC2_CH0/GPIO4)
/GPIO0/REFCLKO: Q2.2 (E), R8.1, S2.1, S2.2, U2.25 (GPIO0/BOOT/ADC2_CH1), U3.14 (~INT/REFCLKO)
/GPIO12: JP3.2 (C), U2.14 (MTDI/GPIO12/ADC2_CH5)
/GPIO13: JP5.2 (C), U2.16 (MTCK/GPIO13/ADC2_CH4)
/GPIO14: JP4.2 (C), U2.13 (MTMS/GPIO14/ADC2_CH6)
/GPIO15: JP2.2 (C), U2.23 (MTDO/GPIO15/ADC2_CH3)
/LAN8720A/GPIO5/~RST: C11.1, R23.1, U2.29 (GPIO5), U3.15 (~RST)
/LAN8720A/GPIO18/MDIO: R19.1, U2.30 (GPIO18)
/LAN8720A/GPIO19/EMAC_TXD0: R13.1, U2.31 (GPIO19)
/LAN8720A/GPIO21/EMAC_TXEN: R15.1, U2.33 (GPIO21)
/LAN8720A/GPIO22/EMAC_TXD1: R14.1, U2.36 (GPIO22)
/LAN8720A/GPIO23/MDC: R20.1, U2.37 (GPIO23)
/LAN8720A/GPIO25/EMAC_RXD0: R16.1, U2.10 (DAC_1/ADC2_CH8/GPIO25)
/LAN8720A/GPIO26/EMAC_RXD1: R17.1, U2.11 (DAC_2/ADC2_CH9/GPIO26)
/LAN8720A/GPIO27/EMAC_CRS_DV: R18.1, U2.12 (ADC2_CH7/GPIO27)
/LTE/AP_READY: U4.2 (AP_READY), U5.9 (A8)
/LTE/CTS: U4.64 (CTS), U5.6 (A5)
/LTE/DCD: U4.63 (DCD), U5.7 (A6)
/LTE/DTR: U4.66 (DTR), U5.4 (A3)
/LTE/LTE_AP_READY: J5.11, R55.2
/LTE/LTE_PWRKEY: J5.15, R35.1
/LTE/LTE_RESET_N: J5.17, R36.1
/LTE/LTE_STATUS: J5.13, R57.1, U6.17 (B3)
/LTE/LTE_UART_DBG_RXD: J5.5, R59.2
/LTE/LTE_UART_DBG_TXD: J5.1, R58.2
/LTE/LTE_UART_DTR: J5.3, R50.2
/LTE/RI: U4.62 (RI), U5.8 (A7)
/LTE/RTS: U4.65 (RTS), U5.5 (A4)
/LTE/RXD: U4.68 (RXD), U5.1 (A1)
/LTE/STATUS: U4.61 (STATUS), U6.4 (A3)
/LTE/TXD: U4.67 (TXD), U5.3 (A2)
/LTE/VDD_EXT: C38.1, C39.1, C40.1, C41.1, C42.1, C43.1, R43.2, R45.2, U4.7 (VDD_EXT), U5.2 (VCCA), U6.2 (VCCA)
/LTE_UART_CTS: J5.4, R52.2
/LTE_UART_DCD: J5.2, R53.2
/LTE_UART_RI: J5.6, R54.2
/LTE_UART_RTS: J5.8, R51.2
/LTE_UART_RXD: J5.10, R48.2
/LTE_UART_TXD: J5.12, R49.2
/MISO: JP3.1 (A), R10.1
/MOSI: JP5.1 (A), R12.1
/MTCK: J2.4 (SWCLK/TCK), JP5.3 (B), R2.1
/MTDI: J2.8 (NC/TDI), JP3.3 (B), R4.1
/MTDO: J2.6 (SWO/TDO), JP2.3 (B)
/MTMS: J2.2 (SWDIO/TMS), JP4.3 (B), R3.1
/RTC/RTC_MFP: J5.14, R60.2, U7.7 (MFP)
/RTC/SCL: J5.7, U7.6 (SCL)
/RTC/SDA: J5.9, U7.5 (SDA)
/SAM4E_INT: J4.3, U2.24 (ADC2_CH2/GPIO2)
/SCK: JP4.1 (A), R11.1
/U0RXD: J3.1, U2.34 (U0RXD/GPIO3)
/U0TXD: J3.3, U2.35 (U0TXD/GPIO1)
/~DTR0: J3.5, Q2.3 (C), R6.1
/~RST0: J3.7, Q1.2 (E), R7.1
Earth_Protective: J1.1, J3.9, J6.SH, J7.SH, JP1.1 (A), RV1.1, RV2.2
GND: BT1.2 (-), C1.2, C2.2, C3.2, C4.2, C5.2, C6.2, C7.2, C8.2, C9.2, C10.2, C11.2, C12.2, C13.2, C14.2, C15.2, C16.2, C17.2, C18.2, C19.2, C20.2, C21.2, C22.2, C23.2, C24.2, C25.2, C26.2, C27.2, C28.2, C29.2, C30.2, C31.2, C32.2, C33.2, C34.2, C35.2, C36.2, C37.2, C38.2, C39.2, C40.2, C41.2, C42.2, C43.2, C44.2, C45.2, C46.2, C47.2, C48.2, C49.2, C50.2, C51.2, C52.2, C53.1, C54.1, D1.2 (GND), D2.1 (A1), J1.2, J2.3 (GND), J2.5 (GND), J2.9 (GNDDetect), J3.4, J3.6, J3.8, J3.10, J4.7, J4.9, J5.16, J5.18, J6.8, JP1.2 (B), Q3.2 (E), Q4.2 (E), R26.2, R32.2, R33.2, R34.2, R37.2, R38.2, R44.2, R46.1, R47.1, R56.1, RV1.2, RV2.1, S1.3, S1.4, S2.3, S2.4, U1.3 (GND), U2.1 (GND), U2.15 (GND), U2.38 (GND), U2.39 (GND_THERMAL), U3.25 (VSS), U4.8 (GND), U4.9 (GND), U4.19 (GND), U4.22 (GND), U4.36 (GND), U4.46 (GND), U4.48 (GND), U4.50 (GND), U4.51 (GND), U4.52 (GND), U4.53 (GND), U4.54 (GND), U4.56 (GND), U4.72 (GND), U4.85 (GND), U4.86 (GND), U4.87 (GND), U4.88 (GND), U4.89 (GND), U4.90 (GND), U4.91 (GND), U4.92 (GND), U4.93 (GND), U4.94 (GND), U4.95 (GND), U4.96 (GND), U4.97 (GND), U4.98 (GND), U4.99 (GND), U4.100 (GND), U4.101 (GND), U4.102 (GND), U4.103 (GND), U4.104 (GND), U4.105 (GND), U4.106 (GND), U4.107 (GND), U4.108 (GND), U4.109 (GND), U4.110 (GND), U4.111 (GND), U4.112 (GND), U5.11 (GND), U6.11 (GND), U7.4 (VSS), Y1.2, Y1.4
unnamed: BT1.1 (+), D3.2 (A)
unnamed: C9.1, R21.1, Y1.1
unnamed: C10.1, R22.1, Y1.3
unnamed: C30.1, C31.1, C32.1, C33.1, C34.1, C35.1, C36.1, C37.1, L4.2, U4.57 (VBAT_RF), U4.58 (VBAT_RF), U4.59 (VBAT_BB), U4.60 (VBAT_BB)
unnamed: C25.1, D1.1 (IO1), J7.1 (VCC), R39.1, U4.14 (USIM_VDD)
unnamed: C26.1, D1.3 (IO2), J7.2 (RST), R40.1
unnamed: C27.1, D1.4 (IO3), J7.3 (CLK), R41.1
unnamed: C29.1, D1.5 (IO4), J7.7 (I/O), R39.2, R42.1
unnamed: D3.1 (K), R61.2
unnamed: C3.1, C4.1, C5.1, C6.1, J2.1 (VTref), L2.2, R2.2, R3.2, R4.2, U2.2 (3V3)
unnamed: J2.10 (~RESET), R1.1
unnamed: J4.4, R9.2
unnamed: J4.6, R10.2
unnamed: J4.8, R11.2
unnamed: J4.10, R12.2
unnamed: J6.9, R33.1
unnamed: J6.11, R32.1
unnamed: C22.1, J6.2 (TCT), J6.5 (RCT), R31.1
unnamed: J6.4 (RD+), R28.1, U3.23 (RXP)
unnamed: J6.6 (RD-), R27.1, U3.22 (RXN)
unnamed: J6.1 (TD+), R30.1, U3.21 (TXP)
unnamed: J6.3 (TD-), R29.1, U3.20 (TXN)
unnamed: J7.5 (GND), U4.10 (USIM_GND)
unnamed: Q1.1 (B), R6.2
unnamed: C8.1, Q1.3 (C), R1.2, R5.1, S1.1, S1.2, U1.1 (VOUT), U2.3 (EN/CHIP_PU)
unnamed: Q2.1 (B), R7.2
unnamed: Q3.1 (B), R35.2, R37.1
unnamed: C28.1, Q3.3 (C), U4.21 (PWRKEY)
unnamed: Q4.1 (B), R36.2, R38.1
unnamed: Q4.3 (C), U4.20 (RESET_N)
unnamed: C1.1, C2.1, C7.1, L1.2, R5.2, R8.2, U1.2 (VDD)
unnamed: R18.2, U3.11 (CRS_DV/MODE2)
unnamed: J6.10, U3.3 (LED1/REGOFF)
unnamed: J6.12, R34.1, U3.2 (LED2/~INTSEL)
unnamed: R20.2, U3.13 (MDC)
unnamed: R19.2, R24.1, U3.12 (MDIO)
unnamed: R26.1, U3.24 (RBIAS)
unnamed: R16.2, U3.8 (RXD0/MODE0)
unnamed: R17.2, U3.7 (RXD1/MODE1)
unnamed: R25.1, U3.10 (RXER/PHYAD0)
unnamed: R13.2, U3.17 (TXD0)
unnamed: R14.2, U3.18 (TXD1)
unnamed: R15.2, U3.16 (TXEN)
unnamed: C14.1, C15.1, C16.1, C17.1, C18.1, C19.1, C20.1, C21.1, C23.1, C24.1, L3.1, R23.2, R24.2, R25.2, R27.2, R28.2, R29.2, R30.2, R31.2, U3.1 (VDD2A), U3.9 (VDDIO), U3.19 (VDD1A)
unnamed: C12.1, C13.1, U3.6 (VDDCR)
unnamed: R21.2, U3.5 (XTAL1/CLKIN)
unnamed: R22.2, U3.4 (XTAL2)
unnamed: U4.11 (DBG_RXD), U6.3 (A2)
unnamed: U4.12 (DBG_TXD), U6.1 (A1)
unnamed: R41.2, U4.16 (USIM_CLK)
unnamed: R42.2, U4.15 (USIM_DATA)
unnamed: R40.2, U4.17 (USIM_RST)
unnamed: R48.1, U5.20 (B1)
unnamed: R49.1, U5.18 (B2)
unnamed: R50.1, U5.17 (B3)
unnamed: R51.1, U5.16 (B4)
unnamed: R52.1, U5.15 (B5)
unnamed: R53.1, U5.14 (B6)
unnamed: R54.1, U5.13 (B7)
unnamed: R55.1, U5.12 (B8)
unnamed: R43.1, R44.1, U5.10 (OE)
unnamed: C44.1, C46.1, L5.1, U5.19 (VCCB)
unnamed: R47.2, U6.5 (A4), U6.6 (A5), U6.7 (A6), U6.8 (A7), U6.9 (A8)
unnamed: R58.1, U6.20 (B1)
unnamed: R59.1, U6.18 (B2)
unnamed: R56.2, U6.12 (B8), U6.13 (B7), U6.14 (B6), U6.15 (B5), U6.16 (B4)
unnamed: R45.1, R46.2, U6.10 (OE)
unnamed: C45.1, C47.1, L6.1, U6.19 (VCCB)
unnamed: C52.1, R61.1, U7.3 (VBAT)
unnamed: C50.1, C51.1, L7.2, U7.8 (VCC)
unnamed: C53.2, U7.1 (X1), XTAL1.2
unnamed: C54.2, U7.2 (X2), XTAL1.1

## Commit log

2021-10-17 Initial files added
2021-10-19 Changed board schematic
2021-12-15 Eagle schematic changed
2022-02-09 Added RS485 Interface Module
2022-02-11 Updated schematic
2022-02-13 Logic unit schematic updated
2023-04-20 PLC Update
    Added Ethernet module.
2023-06-25 PLC board design
    Verifications and improvements of the hardware design.
2023-12-02 [UPDATE] Refactored repository
    Updated repository with laatest work. Uploaded work that has been made in EAGLE and continued in Kicad. Removed redundant information.
2023-12-03 [UPDATE]
    Finished ESP32 and ESP32-programmer board designs (few corrections to be made when manufacturer is chosen - design rules).
2023-12-03 [UPDATE]
    Fixed design PDF files.
2023-12-03 [Components]
    Completed component lists for ESP32-programmer and ESP32 boards.
2023-12-08 [FIX]
    Updated footprints for tactile switches.
2023-12-08 [UPDATE]
    Refactored schematic for LTE, Power and other schematic sub-sheets.
2023-12-09 [UPDATE]
    First draft of SAM4E-PLC schematic completed.
2023-12-09 [IN PROGRESS]
    SAM4E-PLC PCB design in progress.
2023-12-10 [UPDATE]
    Work in progress.
2023-12-22 [UPDATE]
    Finished ESP32-PLC board design
2023-12-22 [UPDATE]
    Completed SAM4E-PLC board design.
2023-12-22 [Prototype A completed]
    Completed first board prototype design.
2024-06-04 [PLC implementation]
    Added documentation: datasheets and technical papers.
2024-06-05 [Final report]
    Updated images for documentation.
2024-06-05 [Final report]
    Cleared redundant files.
2024-06-08 [Final report]
    Added simple images for ESP32 adn SAM4
2024-06-11 [Libraries]
    Added used libraries for the KiCad projects.
2024-06-12 [Final report]
    Added 3D models.
2024-06-12 [Documents]
    Fixed documentation.
2024-06-13 [PLC]
    Updated PCB PDFs.
2026-04-05 [Refactor] Documentation refactoring
    Sorted documentation and added final report for the device.
